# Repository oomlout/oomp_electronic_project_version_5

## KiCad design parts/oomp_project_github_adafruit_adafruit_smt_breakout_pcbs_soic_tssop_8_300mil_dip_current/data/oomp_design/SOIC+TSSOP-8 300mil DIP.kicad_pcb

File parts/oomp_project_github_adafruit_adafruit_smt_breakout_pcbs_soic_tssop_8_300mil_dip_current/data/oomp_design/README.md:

# OOMP KiCad design copy

Open `SOIC+TSSOP-8 300mil DIP.kicad_pro` (or the `.kicad_pcb` / `.kicad_sch`) in KiCad. Local OOMP libraries are under `libraries/`. Original inputs are preserved in [../original/](../original/).

Only verified unchanged installed KiCad defaults were renamed. Modified, custom, unmatched and unavailable items remain unchanged. Soldering variants are never swapped during conversion. Existing pad coordinates, nets and UUIDs are preserved.

See [conversion_report.yaml](conversion_report.yaml) for every conversion and skip. Copy this directory before editing; regeneration refuses to overwrite edited design files.

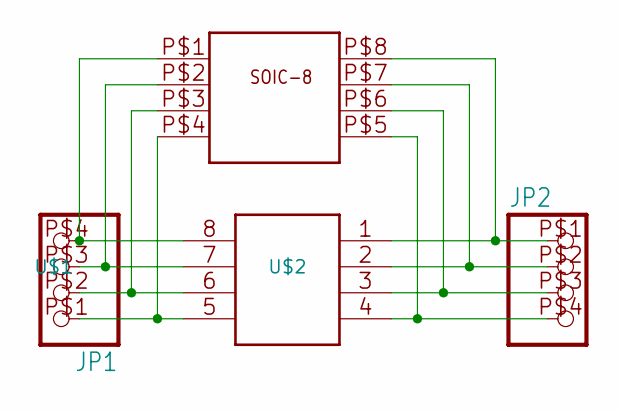
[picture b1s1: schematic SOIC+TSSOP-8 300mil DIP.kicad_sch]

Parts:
JP1, JP2: PINHD-1X4THIN; HEADER1X4
U$1: SO-8; SO-08NMW
U$2: TSSOP-8; TSSOP-8NM

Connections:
unnamed: JP1.P$4 (4), U$1.P$1, U$2.8
unnamed: JP1.P$3 (3), U$1.P$2, U$2.7
unnamed: JP1.P$2 (2), U$1.P$3, U$2.6
unnamed: JP1.P$1 (1), U$1.P$4, U$2.5
unnamed: JP2.P$4 (4), U$1.P$5, U$2.4
unnamed: JP2.P$3 (3), U$1.P$6, U$2.3
unnamed: JP2.P$2 (2), U$1.P$7, U$2.2
unnamed: JP2.P$1 (1), U$1.P$8, U$2.1

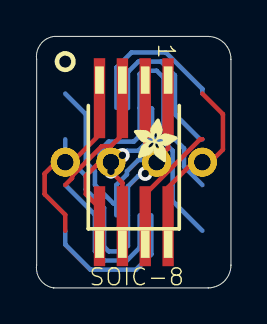
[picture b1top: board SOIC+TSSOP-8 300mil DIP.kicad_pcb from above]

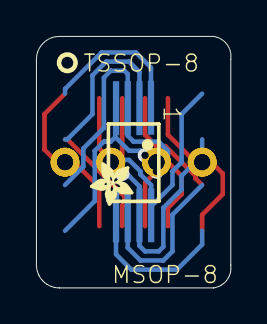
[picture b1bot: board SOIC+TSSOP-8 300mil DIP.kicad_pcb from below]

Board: 2 copper layers, 10.8 x 14.0 mm, 6 parts (2 on the bottom side), 8 nets.

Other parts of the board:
U$3, U$4: ADAFRUIT_2.5MM

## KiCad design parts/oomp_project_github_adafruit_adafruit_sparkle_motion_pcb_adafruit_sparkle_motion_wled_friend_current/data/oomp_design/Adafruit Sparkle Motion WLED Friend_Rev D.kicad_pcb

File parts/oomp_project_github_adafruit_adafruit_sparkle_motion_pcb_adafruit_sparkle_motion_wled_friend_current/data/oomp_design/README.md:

# OOMP KiCad design copy

Open `Adafruit Sparkle Motion WLED Friend_Rev D.kicad_pro` (or the `.kicad_pcb` / `.kicad_sch`) in KiCad. Local OOMP libraries are under `libraries/`. Original inputs are preserved in [../original/](../original/).

Only verified unchanged installed KiCad defaults were renamed. Modified, custom, unmatched and unavailable items remain unchanged. Soldering variants are never swapped during conversion. Existing pad coordinates, nets and UUIDs are preserved.

See [conversion_report.yaml](conversion_report.yaml) for every conversion and skip. Copy this directory before editing; regeneration refuses to overwrite edited design files.

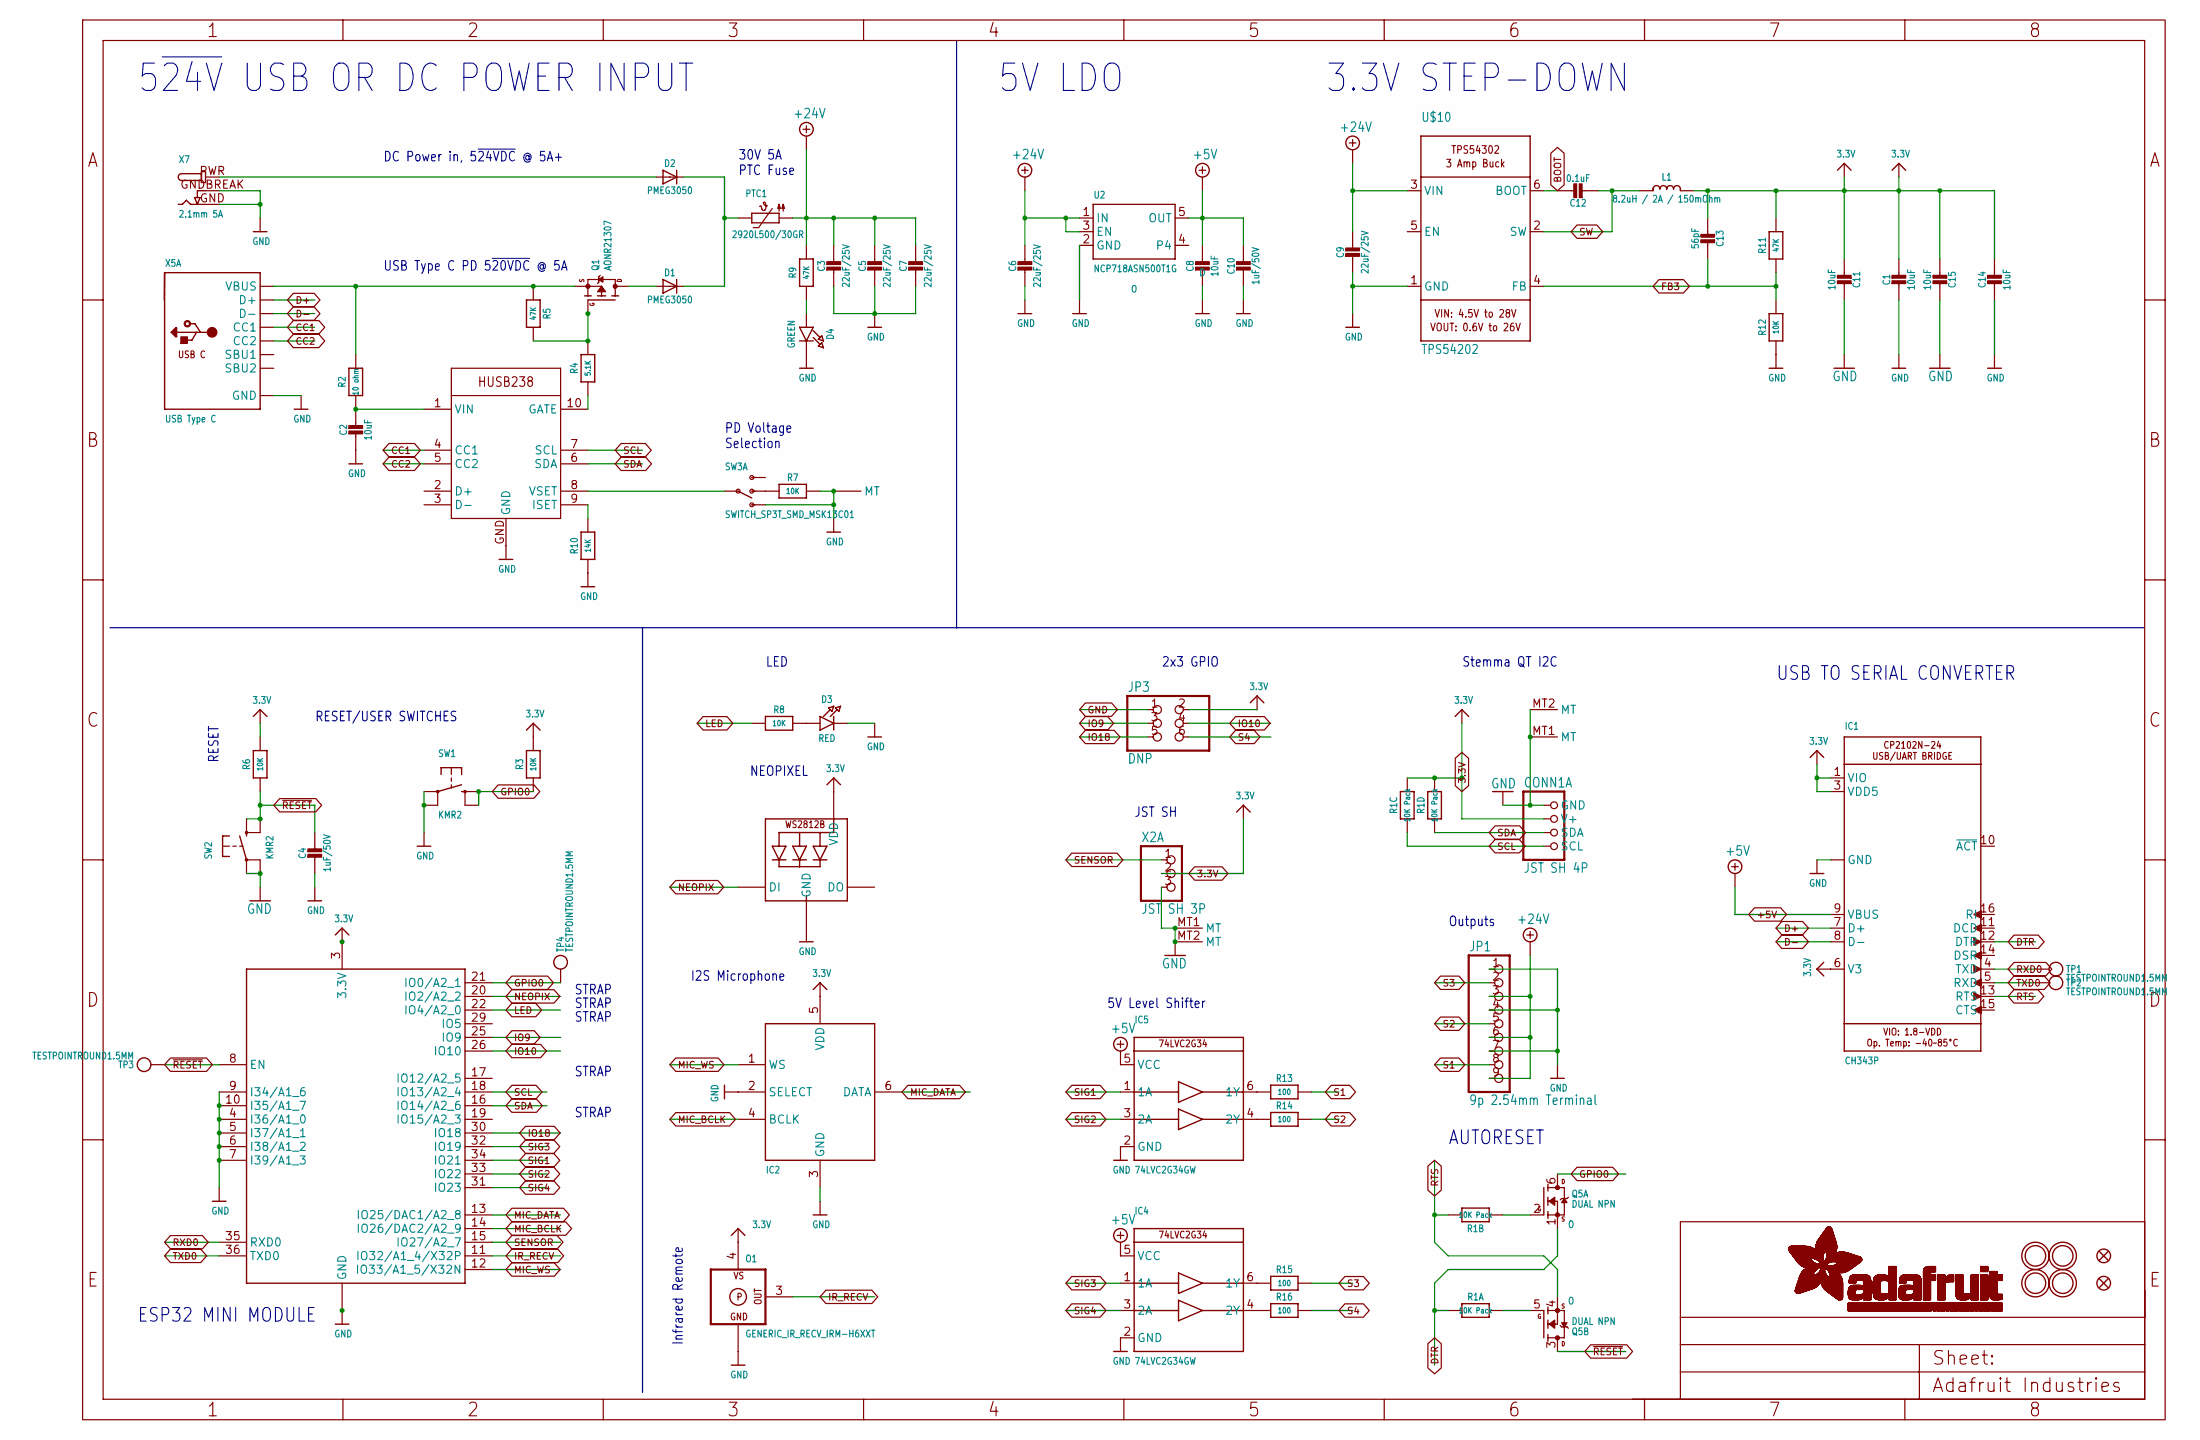
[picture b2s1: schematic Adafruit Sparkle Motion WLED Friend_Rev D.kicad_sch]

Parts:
C1, C2, C8, C11, C14, C15: 10uF; 0805-NO
C3, C5, C6, C7, C9: 22uF/25V; 0805-NO
C4, C10: 1uF/50V; 0603-NO
C12: 0.1uF; 0603-NO
C13: 56pF; 0603-NO
CONN1: JST SH 4P; JST_SH4; LCSC C2845363
D1, D2: PMEG3050; SOD-128
D3: RED; CHIPLED_0603_NOOUTLINE
D4: GREEN; CHIPLED_0603_NOOUTLINE
IC1: CH343P; QFN16_3MM
IC2: ICS-43434; SPH0645LM4H
IC4, IC5: 74LVC2G34GW; SC70-6L
JP1: 9p 2.54mm Terminal; 1X09_2.54MMTERMINAL
JP3: DNP; 2X03_ROUND_70MIL
L1: 8.2uH / 2A / 150mOhm; INDUCTOR_5X5MM_NR5040_NOTHERMALS
LED1: WS2812B_SK6805_1515; SK6805_1515; LCSC C2890035
O1: GENERIC_IR_RECV_IRM-H6XXT; IRM-H6XXT
PTC1: 2920L500/30GR; PTC2920
Q1: AONR21307; POWERDI3333
Q5: DUAL NPN; SOT363; JLC_ROTATION 0
R1: 10K Pack; RESPACK_4X0603
R2: 10 ohm; 0603-NO
R3, R6, R7, R8, R12: 10K; 0603-NO
R4: 5.1K; 0603-NO
R5, R9, R11: 47K; 0603-NO
R10: 14K; 0603-NO
R13, R14, R15, R16: 100; 0603-NO
SW1, SW2: KMR2; BTN_RKB2_4.6X2.8
SW3: SWITCH_SP3T_SMD_MSK13C01; MSK-13C01
TP1, TP2, TP3, TP4: TESTPOINTROUND1.5MM; TESTPOINT_ROUND_1.5MM
U2: NCP718ASN500T1G; SOT23-5; JLC_ROTATION 0
U$10: TPS54202; SOT23-6
U$14, U$20, U$28, U$31: MOUNTINGHOLE2.5; MOUNTINGHOLE_2.5_PLATED
U$34, U$35: FIDUCIAL_1MM
X2: JST SH 3P; JST_SH3
X3: HUSB238; DFN10_3X3MM
X4: ESP32-MINI-1
X5: USB Type C; USB_C_CUSB31-CFM2AX-01-X; LCSC C165948
X7: 2.1mm 5A; DCJACK_2MM_PTH

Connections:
3.3V: C1.1, C11.1, C13.2, C14.1, C15.1, CONN1.2 (V+), IC1.1 (VIO), IC1.3 (VDD5), IC1.6 (V3), IC2.5 (VDD), JP3.2, L1.P$2 (2), LED1.2 (VDD), O1.4 (VS), R1.5 (2), R1.6 (2), R3.2, R6.2, R11.2, X2.2, X4.3 (3.3V)
+5V: C8.1, C10.1, IC1.9 (VBUS), IC4.5 (VCC), IC5.5 (VCC), U2.5 (OUT)
+24V: C3.1, C5.1, C6.1, C7.1, C9.1, JP1.3, JP1.6, JP1.9, PTC1.P$1 (1), R9.2, U2.1 (IN), U2.3 (EN), U$10.3 (VIN)
BOOT: C12.1, U$10.6 (BOOT)
CC1: X3.4 (CC1), X5.A5 (CC1)
CC2: X3.5 (CC2), X5.B5 (CC2)
D+: IC1.7 (D+), X5.A6 (D+), X5.B6 (D+)
D-: IC1.8 (D-), X5.A7 (D-), X5.B7 (D-)
DTR: IC1.12 (DTR), Q5.1 (S), R1.1
FB3: C13.1, R11.1, R12.2, U$10.4 (FB)
GND: C1.2, C2.2, C3.2, C4.2, C5.2, C6.2, C7.2, C8.2, C9.2, C10.2, C11.2, C14.2, C15.2, CONN1.1 (GND), CONN1.MT1 (MT), CONN1.MT2 (MT), D3.C, D4.C, IC1.2 (GND), IC1.THERMAL (GND), IC2.2 (SELECT), IC2.3 (GND), IC4.2 (GND), IC5.2 (GND), JP1.1, JP1.4, JP1.7, JP3.1, LED1.4 (GND), O1.1 (GND), O1.2 (GND), R7.1, R10.1, R12.1, SW1.A, SW1.A' (P1), SW2.A, SW2.A' (P1), SW3.4 (3), SW3.MT1 (MT), SW3.MT2 (MT), SW3.MT3 (MT), SW3.MT4 (MT), U2.2 (GND), U$10.1 (GND), X2.3, X2.MT1 (MT), X2.MT2 (MT), X3.GND, X4.1 (GND), X4.2 (GND), X4.4 (I36/A1_0), X4.5 (I37/A1_1), X4.6 (I38/A1_2), X4.7 (I39/A1_3), X4.9 (I34/A1_6), X4.10 (I35/A1_7), X4.27 (GND), X4.38 (GND), X4.39 (GND), X4.40 (GND), X4.41 (GND), X4.42 (GND), X4.43 (GND), X4.44 (GND), X4.45 (GND), X4.46 (GND), X4.47 (GND), X4.48 (GND), X4.49 (GND), X4.50 (GND), X4.51 (GND), X4.52 (GND), X4.53 (GND), X4.54 (GND), X4.55 (GND), X4.56 (GND), X4.57 (GND), X4.58 (GND), X4.59 (GND), X4.60 (GND), X4.61 (GND), X4.62 (GND), X4.63 (GND), X5.A1B12 (GND), X5.B1A12 (GND), X7.GND, X7.GNDBREAK
GPIO0: Q5.6 (D), R3.1, SW1.B (S), SW1.B' (S1), TP4.P$1, X4.21 (IO0/A2_1)
IO9: JP3.3, X4.25 (IO9)
IO10: JP3.4, X4.26 (IO10)
IO18: JP3.5, X4.30 (IO18)
IR_RECV: O1.3 (OUT), X4.11 (IO32/A1_4/X32P)
LED: R8.1, X4.22 (IO4/A2_0)
MIC_BCLK: IC2.4 (BCLK), X4.14 (IO26/DAC2/A2_9)
MIC_DATA: IC2.6 (DATA), X4.13 (IO25/DAC1/A2_8)
MIC_WS: IC2.1 (WS), X4.12 (IO33/A1_5/X32N)
unnamed: D3.A, R8.2
unnamed: C2.1, R2.1, X3.1 (VIN)
unnamed: Q1.4 (G), R4.2, R5.2
unnamed: R4.1, X3.10 (GATE)
unnamed: SW3.3, X3.8 (VSET)
unnamed: R7.2, SW3.2
unnamed: Q5.5 (G), R1.8 (2)
unnamed: Q5.2 (G), R1.2 (1)
unnamed: D2.A, X7.PWR
unnamed: IC5.6 (1Y), R13.1
unnamed: IC5.4 (2Y), R14.1
unnamed: R10.2, X3.9 (ISET)
unnamed: D1.C, D2.C, PTC1.P$2 (2)
unnamed: D1.A, Q1.5678 (D)
unnamed: D4.A, R9.1
unnamed: IC4.6 (1Y), R15.1
unnamed: IC4.4 (2Y), R16.1
NEOPIX: LED1.1 (DI), X4.20 (IO2/A2_2)
RTS: IC1.13 (RTS), Q5.4 (S), R1.7 (2)
RXD0: IC1.4 (TXD), TP1.P$1, X4.35 (RXD0)
S1: JP1.8, R13.2
S2: JP1.5, R14.2
S3: JP1.2, R15.2
S4: JP3.6, R16.2
SCL: CONN1.4 (SCL), R1.3 (1), X3.7 (SCL), X4.18 (IO13/A2_4)
SDA: CONN1.3 (SDA), R1.4 (1), X3.6 (SDA), X4.16 (IO14/A2_6)
SENSOR: X2.1, X4.15 (IO27/A2_7)
SIG1: IC5.1 (1A), X4.34 (IO21)
SIG2: IC5.3 (2A), X4.33 (IO22)
SIG3: IC4.1 (1A), X4.32 (IO19)
SIG4: IC4.3 (2A), X4.31 (IO23)
SW: C12.2, L1.P$1 (1), U$10.2 (SW)
TXD0: IC1.5 (RXD), TP2.P$1, X4.36 (TXD0)
VBUS1: Q1.1 (S), Q1.2 (S), Q1.3 (S), R2.2, R5.1, X5.A4B9 (VBUS), X5.B4A9 (VBUS)
~RESET: C4.1, Q5.3 (D), R6.1, SW2.B (S), SW2.B' (S1), TP3.P$1, X4.8 (EN)

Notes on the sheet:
2x3 GPIO
PD Voltage Selection
ESP32 MINI MODULE
RESET/USER SWITCHES
USB TO SERIAL CONVERTER
AUTORESET
STRAP
3.3V STEP-DOWN
LED
Infrared Remote
Outputs
NEOPIXEL
USB Type C PD 5~{20VDC} @ 5A
Stemma QT I2C
5V LDO
30V 5A PTC Fuse
5~{24V} USB OR DC POWER INPUT
I2S Microphone
DC Power in, 5~{24VDC} @ 5A+
5V Level Shifter
RESET
JST SH

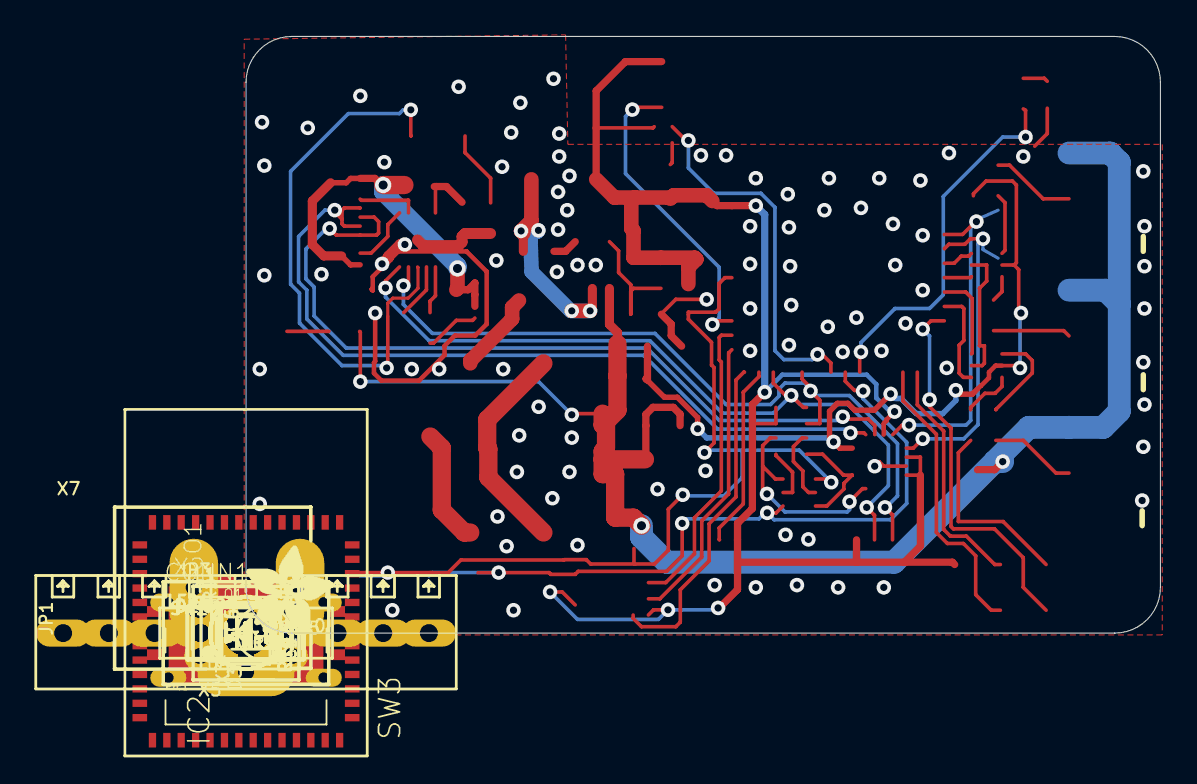
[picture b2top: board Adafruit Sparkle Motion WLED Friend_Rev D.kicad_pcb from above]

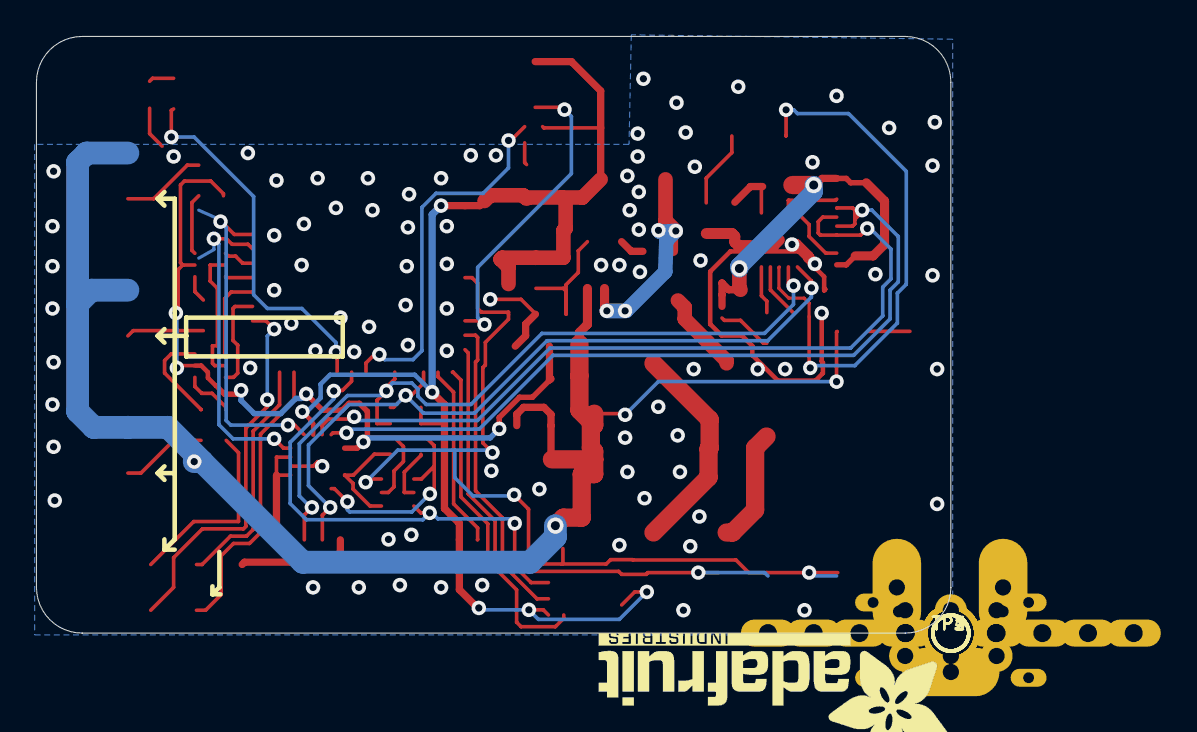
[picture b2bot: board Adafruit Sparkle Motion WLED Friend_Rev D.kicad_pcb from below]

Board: 2 copper layers, 50.8 x 33.1 mm, 123 parts (36 on the bottom side), 55 nets.

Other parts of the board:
PLABEL0: PLABEL0
PLABEL1: PLABEL1
PLABEL2: PLABEL2
PLABEL3: PLABEL3
PLABEL4: PLABEL4
PLABEL6: PLABEL6
PLABEL7: PLABEL7
PLABEL8: PLABEL8
PLABEL9: PLABEL9
PLABEL10: PLABEL10
PLABEL11: PLABEL11
PLABEL13: PLABEL13
PLABEL14: PLABEL14
PLABEL16: PLABEL16
PLABEL17: PLABEL17
PLABEL19: PLABEL19
PLABEL20: PLABEL20
PLABEL21: PLABEL21
PLABEL22: PLABEL22
PLABEL23: PLABEL23
PLABEL24: PLABEL24
PLABEL25: PLABEL25
PLABEL26: PLABEL26
PLABEL27: PLABEL27
PLABEL28: PLABEL28
PLABEL29: PLABEL29
PLABEL30: PLABEL30
PLABEL31: PLABEL31
PLABEL32: PLABEL32
PLABEL33: PLABEL33
PLABEL34: PLABEL34
PLABEL35: PLABEL35
PLABEL36: PLABEL36
PLABEL37: PLABEL37
PLABEL38: PLABEL38
PLABEL39: PLABEL39
PLABEL40: PLABEL40
PLABEL41: PLABEL41
PLABEL42: PLABEL42
PLABEL43: PLABEL43
PLABEL44: PLABEL44
PLABEL45: PLABEL45
PLABEL46: PLABEL46
PLABEL47: PLABEL47
PLABEL48: PLABEL48
PLABEL49: PLABEL49
PLABEL50: PLABEL50
PLABEL51: PLABEL51
PLABEL52: PLABEL52
PLABEL53: PLABEL53
PLABEL54: PLABEL54
PLABEL55: PLABEL55
PLABEL56: PLABEL56
U$46: ADAFRUIT_5MM
U$50: ADAFRUIT_TEXT_20MM

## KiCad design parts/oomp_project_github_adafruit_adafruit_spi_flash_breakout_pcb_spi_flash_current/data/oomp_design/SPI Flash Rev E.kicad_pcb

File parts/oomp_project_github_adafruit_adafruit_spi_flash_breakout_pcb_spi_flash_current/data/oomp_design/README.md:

# OOMP KiCad design copy

Open `SPI Flash Rev E.kicad_pro` (or the `.kicad_pcb` / `.kicad_sch`) in KiCad. Local OOMP libraries are under `libraries/`. Original inputs are preserved in [../original/](../original/).

Only verified unchanged installed KiCad defaults were renamed. Modified, custom, unmatched and unavailable items remain unchanged. Soldering variants are never swapped during conversion. Existing pad coordinates, nets and UUIDs are preserved.

See [conversion_report.yaml](conversion_report.yaml) for every conversion and skip. Copy this directory before editing; regeneration refuses to overwrite edited design files.

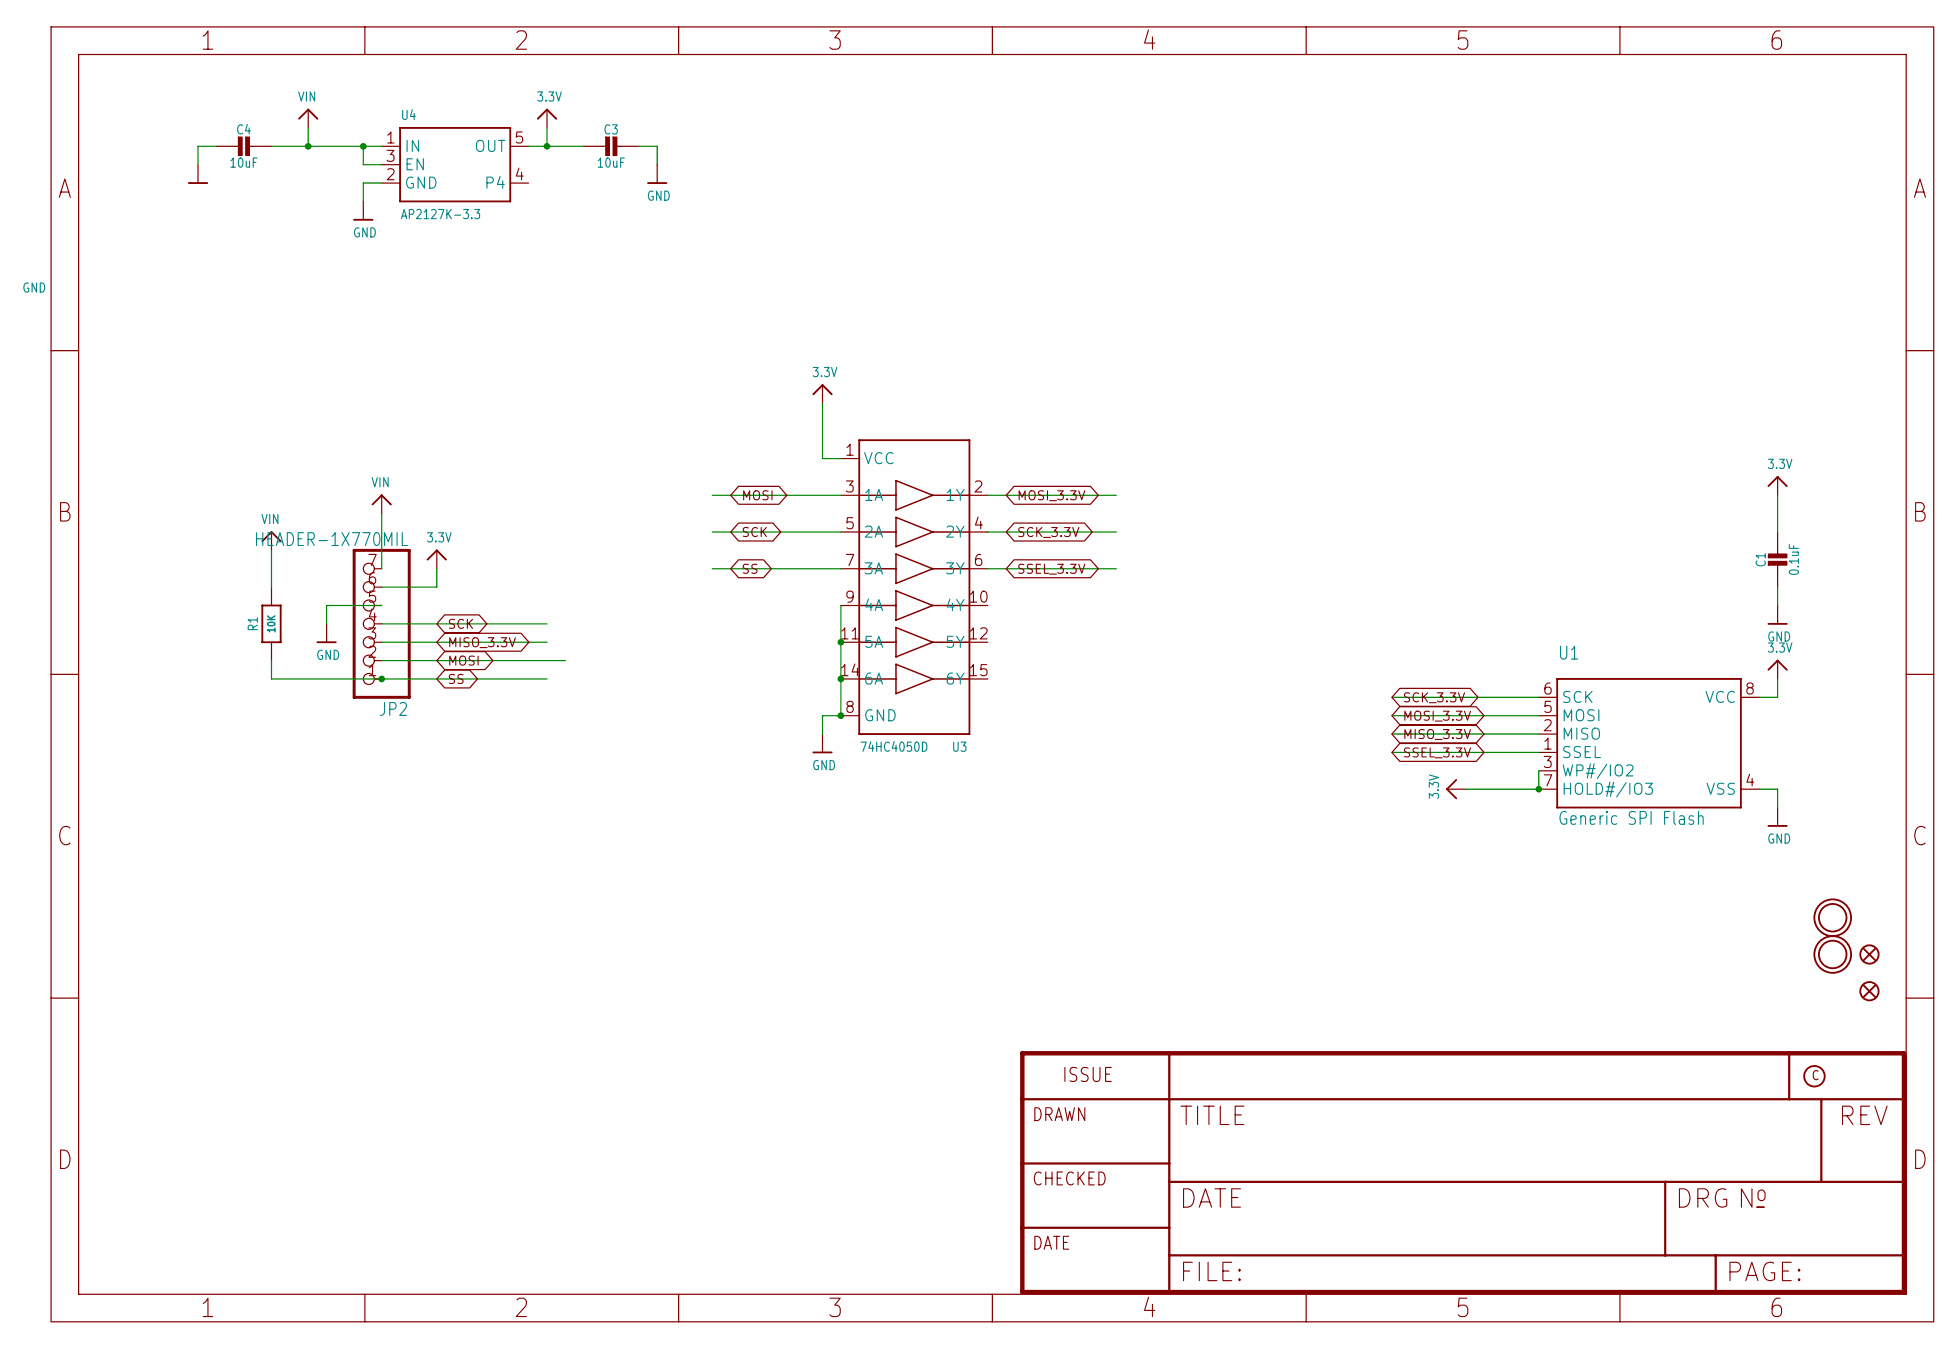
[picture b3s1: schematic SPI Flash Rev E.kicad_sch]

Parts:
C1: 0.1uF; 0603-NO
C3, C4: 10uF; 0805-NO
FID2, FID3: FIDUCIAL_1MM
JP2: HEADER-1X770MIL; 1X07_ROUND_70
R1: 10K; 0603-NO
U1: Generic SPI Flash; SOIC8_208MIL
U3: 74HC4050D; TSSOP16
U4: AP2127K-3.3; SOT23-5; JLC_ROTATION 270
U$16, U$17: MOUNTINGHOLE2.5; MOUNTINGHOLE_2.5_PLATED

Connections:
3.3V: C1.1, C3.2, JP2.6, U1.3 (WP#/IO2), U1.7 (HOLD#/IO3), U1.8 (VCC), U3.1 (VCC), U4.5 (OUT)
GND: C1.2, C3.1, C4.2, JP2.5, U1.4 (VSS), U3.8 (GND), U3.9 (4A), U3.11 (5A), U3.14 (6A), U4.2 (GND)
MISO_3.3V: JP2.3, U1.2 (MISO)
MOSI: JP2.2, U3.3 (1A)
MOSI_3.3V: U1.5 (MOSI), U3.2 (1Y)
SCK: JP2.4, U3.5 (2A)
SCK_3.3V: U1.6 (SCK), U3.4 (2Y)
SS: JP2.1, R1.1, U3.7 (3A)
SSEL_3.3V: U1.1 (SSEL), U3.6 (3Y)
VIN: C4.1, JP2.7, R1.2, U4.1 (IN), U4.3 (EN)

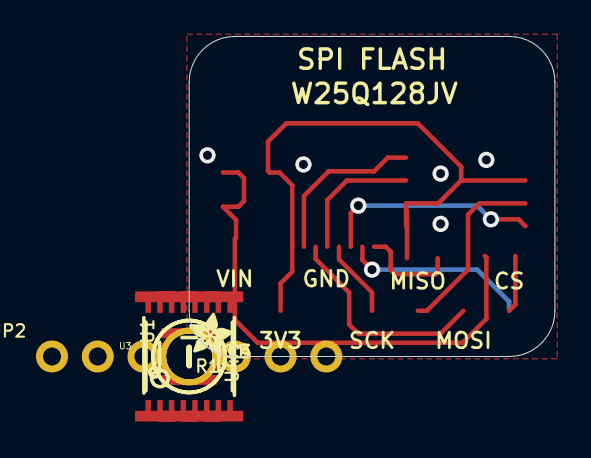
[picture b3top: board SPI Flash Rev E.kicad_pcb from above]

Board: 2 copper layers, 20.3 x 17.8 mm, 14 parts (1 on the bottom side), 10 nets.

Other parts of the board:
U$13: ADAFRUIT_2.5MM
U$21: PCBFEAT-REV-040

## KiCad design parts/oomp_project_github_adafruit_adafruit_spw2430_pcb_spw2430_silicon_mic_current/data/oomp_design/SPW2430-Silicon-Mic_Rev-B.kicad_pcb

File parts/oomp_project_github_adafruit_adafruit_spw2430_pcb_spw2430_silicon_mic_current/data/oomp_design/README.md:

# OOMP KiCad design copy

Open `SPW2430-Silicon-Mic_Rev-B.kicad_pro` (or the `.kicad_pcb` / `.kicad_sch`) in KiCad. Local OOMP libraries are under `libraries/`. Original inputs are preserved in [../original/](../original/).

Only verified unchanged installed KiCad defaults were renamed. Modified, custom, unmatched and unavailable items remain unchanged. Soldering variants are never swapped during conversion. Existing pad coordinates, nets and UUIDs are preserved.

See [conversion_report.yaml](conversion_report.yaml) for every conversion and skip. Copy this directory before editing; regeneration refuses to overwrite edited design files.

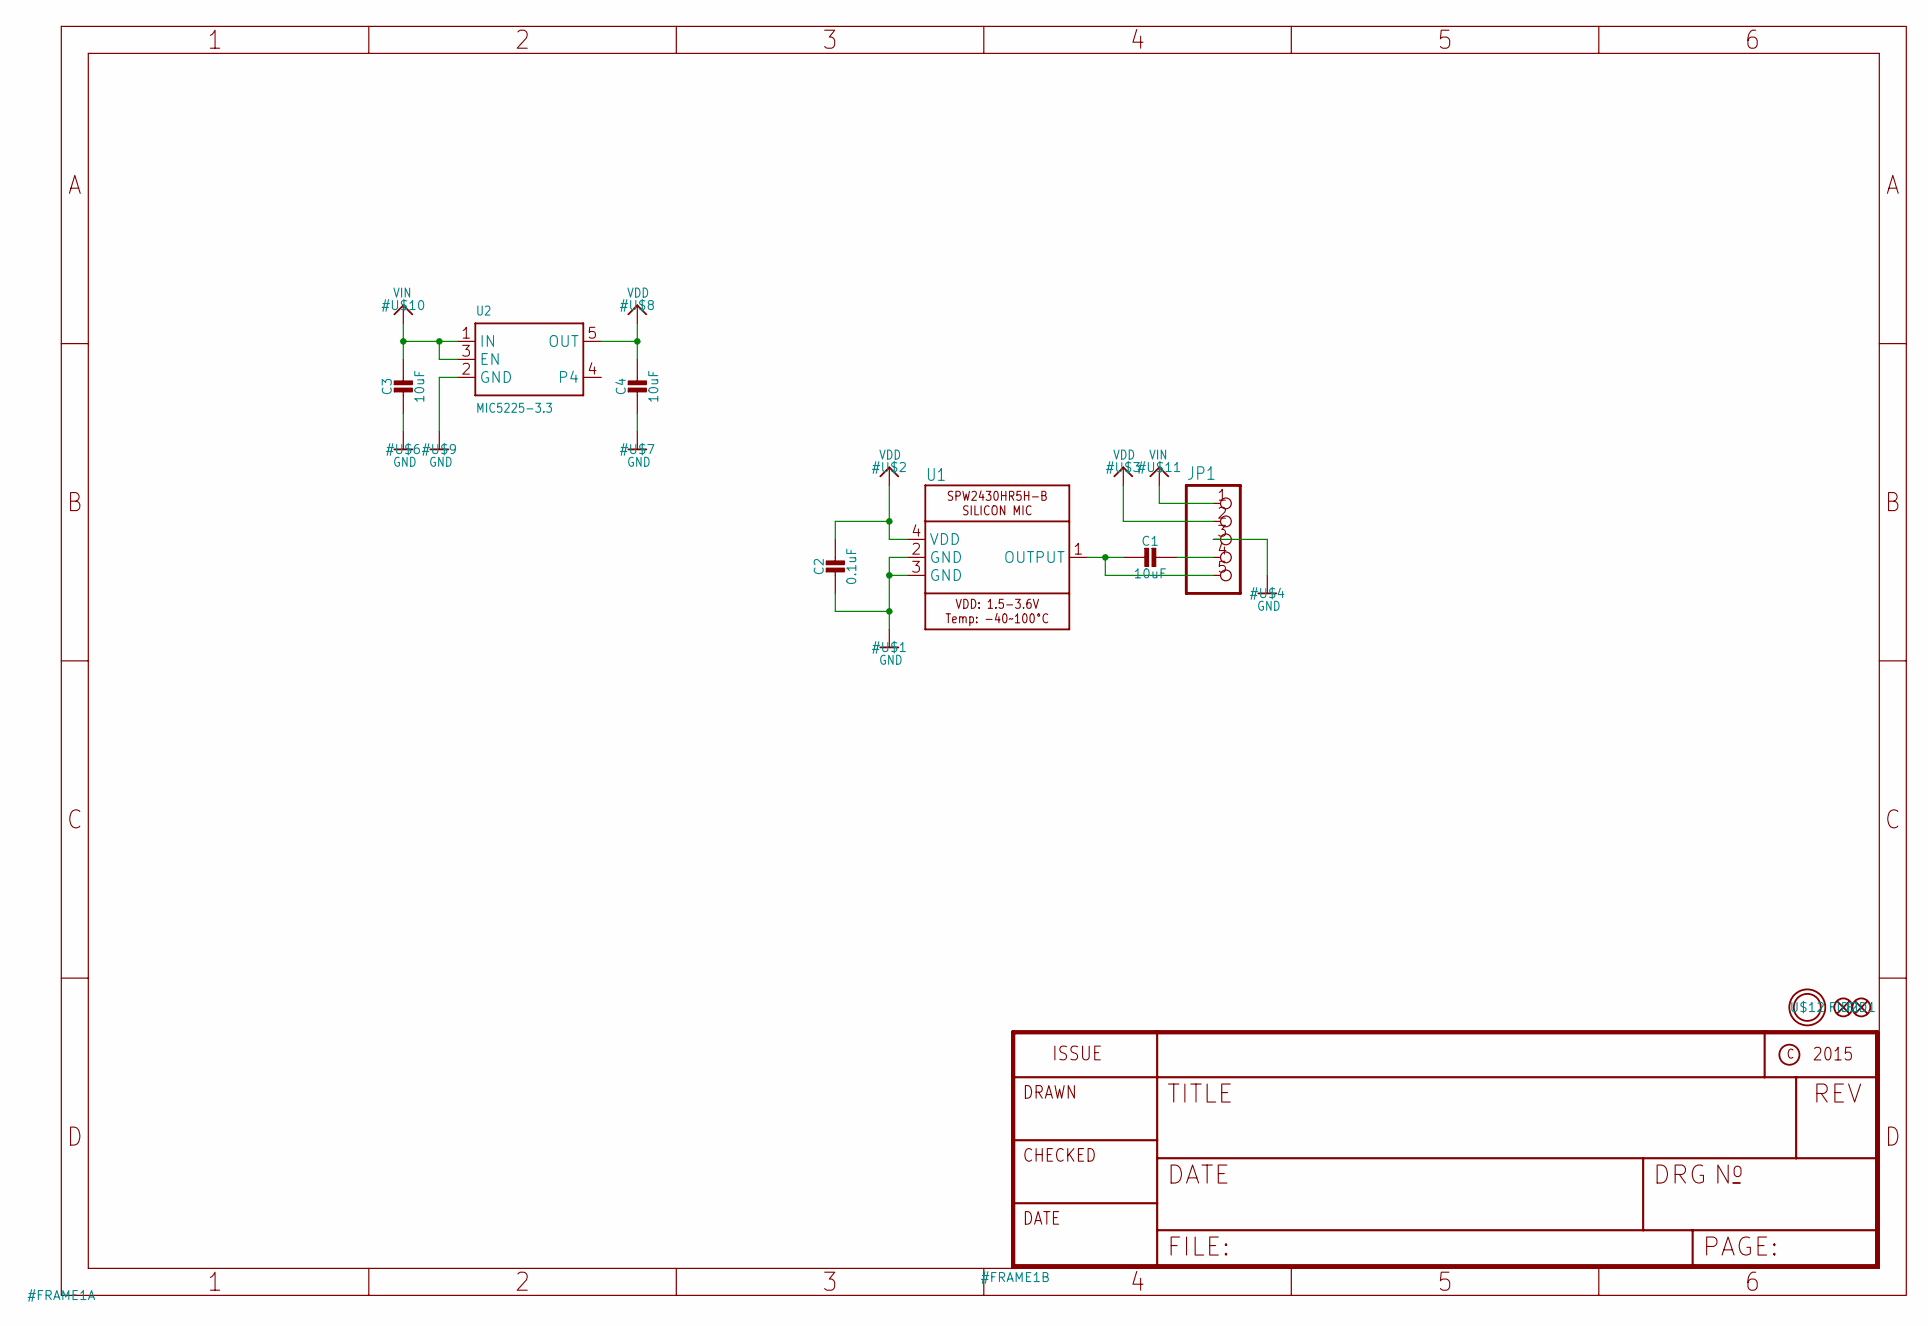
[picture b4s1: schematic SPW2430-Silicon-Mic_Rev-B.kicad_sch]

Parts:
C1, C3, C4: 10uF; 0805-NO
C2: 0.1uF; 0805-NO
FID1, FID2: FIDUCIAL""; FIDUCIAL_1MM
JP1: HEADER-1X576MIL; 1X05_ROUND_76
U1: SPW2430HR5H-B
U2: MIC5225-3.3; SOT23-5
U$12: MOUNTINGHOLE2.5; MOUNTINGHOLE_2.5_PLATED

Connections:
GND: C2.2, C3.2, C4.2, JP1.3, U1.2 (GND), U1.3 (GND), U2.2 (GND)
unnamed: C1.2, JP1.5, U1.1 (OUTPUT)
unnamed: C1.1, JP1.4
VDD: C2.1, C4.1, JP1.2, U1.4 (VDD), U2.5 (OUT)
VIN: C3.1, JP1.1, U2.1 (IN), U2.3 (EN)

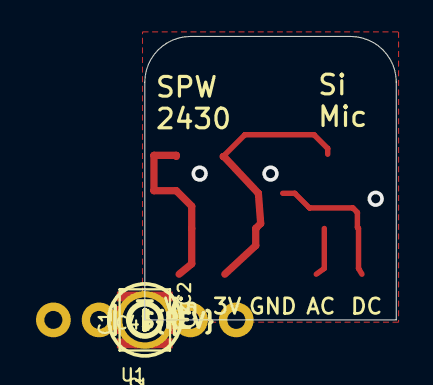
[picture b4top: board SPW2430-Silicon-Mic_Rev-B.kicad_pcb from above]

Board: 2 copper layers, 14.0 x 15.7 mm, 12 parts (1 on the bottom side), 5 nets.

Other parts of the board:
U$5: ADAFRUIT_3.5MM
U$13: PCBFEAT-REV-040
